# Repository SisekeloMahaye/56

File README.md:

# Group 57 Miro Mouse Project

## Overview
This repository contains the documentation for Group 57's Miro Mouse project. The Miro Mouse is a small robotic platform designed for navigating mazes autonomously.

## Team Members
- MHYSIS001: Responsible for the power subsystem.
- ZKHMUS002: Responsible for the sensing subsystem.

## Subsystems
### Power Subsystem (MHYSIS001)
The power subsystem manages the energy requirements of the Miro Mouse. It includes components such as batteries.

### Sensing Subsystem (ZKHMUS002)
The sensing subsystem is responsible for gathering information about the environment. It includes sensors such as infrared sensors, and any other sensors needed for maze navigation.

## Repository Structure
- `power_subsystem/`: Contains documentation related to the power subsystem.
- `sensing_subsystem/`: Contains documentation related to the sensing subsystem.
- `shared/`: Contains documentation shared between the subsystems.

## Installation
1. Clone this repository to your local machine.
2. Navigate to the relevant subsystem directory (`power_subsystem/` or `sensing_subsystem/`).
3. Follow the instructions in the README file located in each subsystem directory to set up and run the code.

## Contribution Guidelines
If you would like to contribute to this project, please follow these guidelines:
- Fork the repository.
- Create a new branch for your feature or bug fix.
- Make your changes.
- Test your changes thoroughly.
- Create a pull request detailing your changes.

## License
[Creative Commons Attribution 4.0 International license](https://choosealicense.com/licenses/cc-by-4.0/)

## Acknowledgements
- This project is developed as part of [Course EEE3088F] at [University of Cape Town].

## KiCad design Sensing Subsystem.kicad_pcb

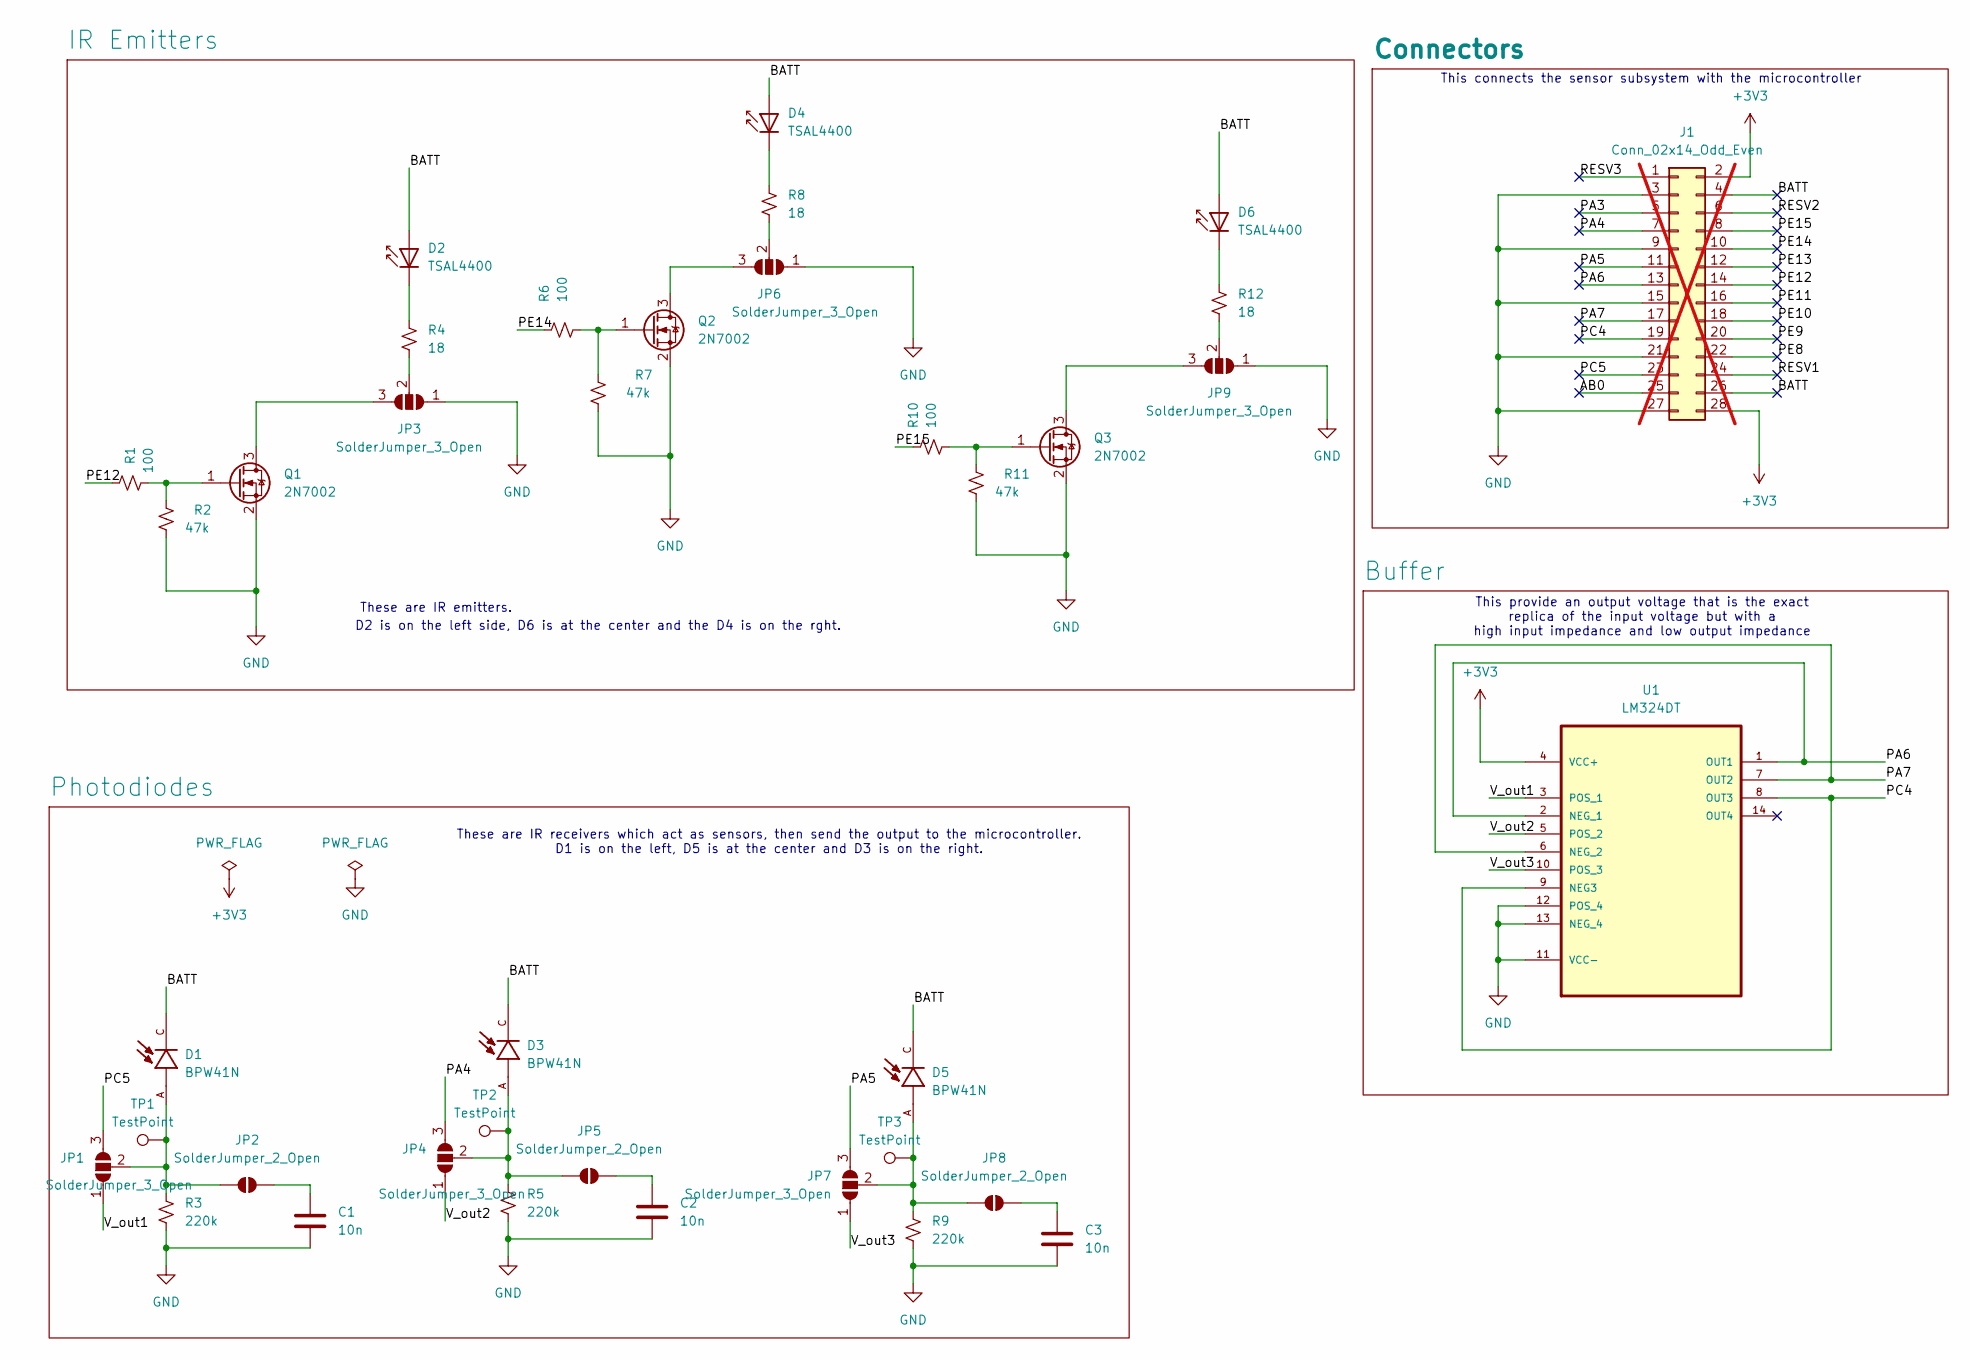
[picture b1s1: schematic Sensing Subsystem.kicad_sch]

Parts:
C1, C2, C3: 10n; C_0402_1005Metric
D1, D3, D5: BPW41N; DIO_BPW41N; PARTREV 1.6
D2, D4, D6: TSAL4400; LED_D1.8mm_W1.8mm_H2.4mm_Horizontal_O3.81mm_Z4.9mm
J1: Conn_02x14_Odd_Even; PinHeader_2x14_P1.00mm_Vertical; not fitted
JP1, JP3, JP4, JP6, JP7, JP9: SolderJumper_3_Open; SolderJumper-3_P1.3mm_Open_RoundedPad1.0x1.5mm_NumberLabels
JP2, JP5, JP8: SolderJumper_2_Open; SolderJumper-2_P1.3mm_Open_RoundedPad1.0x1.5mm
Q1, Q2, Q3: 2N7002; SOT-23
R1, R6, R10: 100; R_0402_1005Metric
R2, R7, R11: 47k; R_0402_1005Metric
R3, R5: 220k; R_0603_1608Metric
R4, R8, R12: 18; R_0402_1005Metric
R9: 220k; R_0402_1005Metric
TP1, TP2, TP3: TestPoint; TestPoint_Pad_D1.5mm
U1: LM324DT; SOIC127P600X175-14N; MPN LM324DT

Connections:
+3V3: J1.2, J1.28, U1.4 (VCC+)
/AB0: J1.25
/BATT: D1.C, D2.2 (A), D3.C, D4.2 (A), D5.C, D6.2 (A), J1.4, J1.26
/PA3: J1.5
/PA4: J1.7, JP4.3 (B)
/PA5: J1.11, JP7.3 (B)
/PA6: J1.13, U1.1 (OUT1), U1.2 (NEG_1)
/PA7: J1.17, U1.6 (NEG_2), U1.7 (OUT2)
/PC4: J1.19, U1.8 (OUT3), U1.9 (NEG3)
/PC5: J1.23, JP1.3 (B)
/PE8: J1.22
/PE9: J1.20
/PE10: J1.18
/PE11: J1.16
/PE12: J1.14, R1.1
/PE13: J1.12
/PE14: J1.10, R6.1
/PE15: J1.8, R10.1
/RESV1: J1.24
/RESV2: J1.6
/RESV3: J1.1
/V_out1: JP1.1 (A), U1.3 (POS_1)
/V_out2: JP4.1 (A), U1.5 (POS_2)
/V_out3: JP7.1 (A), U1.10 (POS_3)
GND: C1.2, C2.2, C3.2, J1.3, J1.9, J1.15, J1.21, J1.27, JP3.1 (A), JP6.1 (A), JP9.1 (A), Q1.2 (S), Q2.2 (S), Q3.2 (S), R2.2, R3.2, R5.2, R7.2, R9.2, R11.2, U1.11 (VCC-), U1.12 (POS_4), U1.13 (NEG_4)
unnamed: D2.1 (K), R4.1
unnamed: D4.1 (K), R8.1
unnamed: D6.1 (K), R12.1
unnamed: D1.A, JP1.2 (C), JP2.1 (A), R3.1, TP1.1
unnamed: C1.1, JP2.2 (B)
unnamed: JP3.3 (B), Q1.3 (D)
unnamed: JP3.2 (C), R4.2
unnamed: D3.A, JP4.2 (C), JP5.1 (A), R5.1, TP2.1
unnamed: C2.1, JP5.2 (B)
unnamed: JP6.3 (B), Q2.3 (D)
unnamed: JP6.2 (C), R8.2
unnamed: D5.A, JP7.2 (C), JP8.1 (A), R9.1, TP3.1
unnamed: C3.1, JP8.2 (B)
unnamed: JP9.3 (B), Q3.3 (D)
unnamed: JP9.2 (C), R12.2
unnamed: Q1.1 (G), R1.2, R2.1
unnamed: Q2.1 (G), R6.2, R7.1
unnamed: Q3.1 (G), R10.2, R11.1

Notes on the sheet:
This connects the sensor subsystem with the microcontroller
D2 is on the left side, D6 is at the center and the D4 is on the rght.
This provide an output voltage that is the exact replica of the input voltage but with a high input impedance and low output impedance
These are IR emitters.
These are IR receivers which act as sensors, then send the output to the microcontroller. D1 is on the left, D5 is at the center and D3 is on the right.

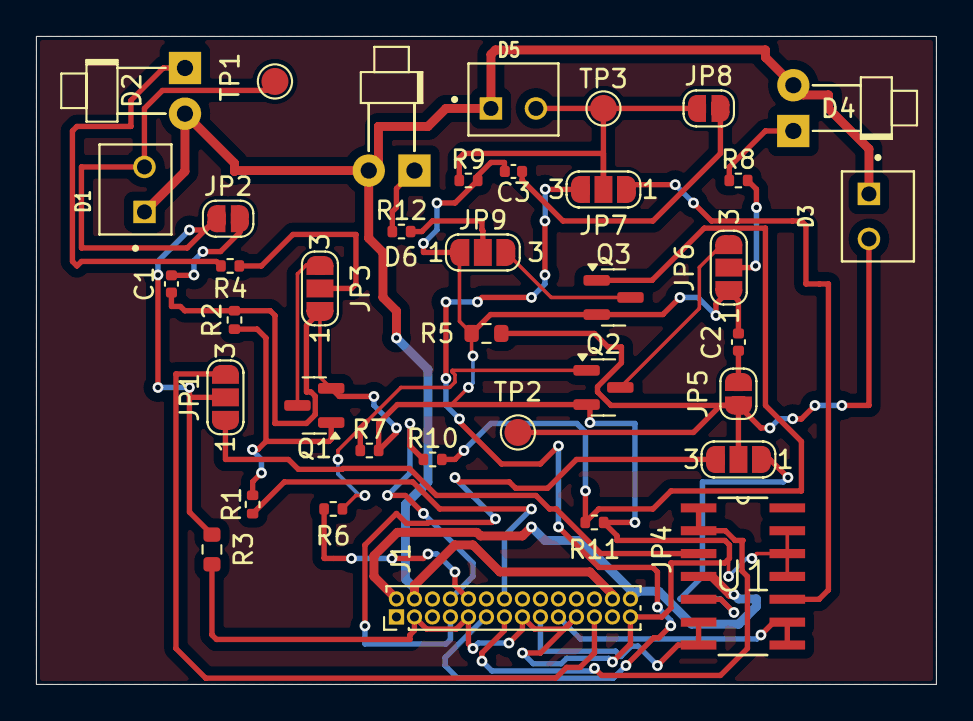
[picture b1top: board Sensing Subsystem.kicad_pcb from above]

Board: 2 copper layers, 50.0 x 36.0 mm, 38 parts (0 on the bottom side), 33 nets.

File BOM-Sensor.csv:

Comment,Designator,Footprint,LCSC
BPW41N,"D1,D3,D5",DIO_BPW41N,C142586
10n,"C1,C2,C3",C_0402_1005Metric,C15195
220k,"R3,R5,R9",R_0603_1608Metric,C22939
15,"R12,R4,R8",R_0402_1005Metric,C25756
47k,"R11,R2,R7",R_0402_1005Metric,C25792
100,"R1,R10,R6",R_0402_1005Metric,C4109
LM324DT,U1,SOIC127P600X175-14N,C71035
2N7002,"Q1,Q2,Q3",SOT-23,C8545
TSAL4400,"D2,D4,D6",LED_D1.8mm_W1.8mm_H2.4mm_Horizontal_O3.81mm_Z4.9mm,C94135

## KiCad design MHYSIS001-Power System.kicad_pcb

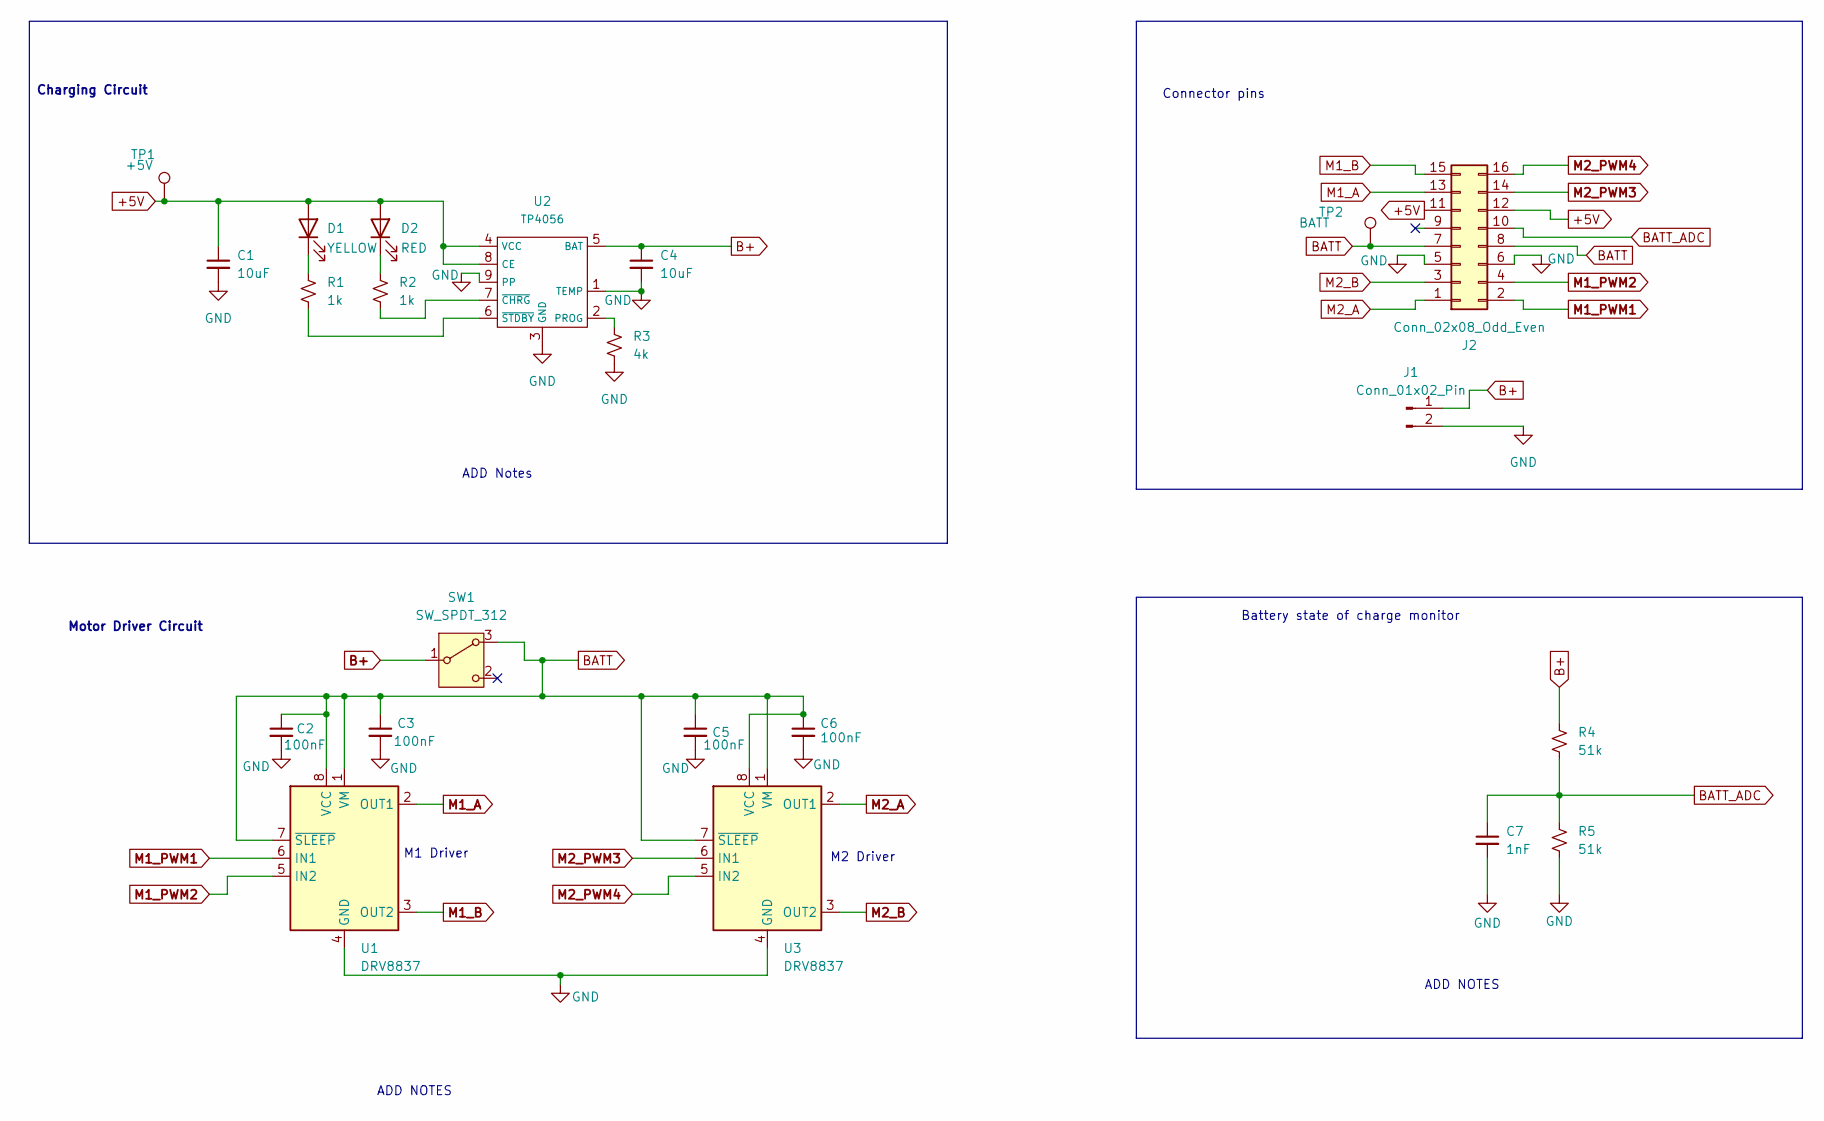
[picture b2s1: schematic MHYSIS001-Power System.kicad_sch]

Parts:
C1, C4: 10uF; C_0603_1608Metric
C2, C3, C5, C6: 100nF; C_0603_1608Metric
C7: 1nF; C_0603_1608Metric
D1: YELLOW; LED_0603_1608Metric
D2: RED; LED_0603_1608Metric
J1: Conn_01x02_Pin; JST_PH_B2B-PH-K_1x02_P2.00mm_Vertical
J2: Conn_02x08_Odd_Even; PinHeader_2x08_P2.54mm_Vertical
R1, R2: 1k; R_0603_1608Metric
R3: 4k; R_0603_1608Metric
R4, R5: 51k; R_0603_1608Metric
SW1: SW_SPDT_312; mySwitch
TP1: +5V; TestPoint_Pad_D1.0mm
TP2: BATT; TestPoint_Pad_D1.0mm
U1, U3: DRV8837; WSON-8-1EP_2x2mm_P0.5mm_EP0.9x1.6mm
U2: TP4056; SOIC-8-1EP_3.9x4.9mm_P1.27mm_EP2.29x3mm

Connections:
+5V: C1.1, D1.2 (A), D2.2 (A), J2.11, J2.12, TP1.1, U2.4 (VCC), U2.8 (CE)
B+: C4.1, J1.1, R4.1, SW1.1 (B), U2.5 (BAT)
BATT: C2.1, C3.1, C5.1, C6.1, J2.7, J2.8, SW1.3 (A), TP2.1, U1.1 (VM), U1.7 (~SLEEP), U1.8 (VCC), U3.1 (VM), U3.7 (~SLEEP), U3.8 (VCC)
BATT_ADC: C7.1, J2.10, R4.2, R5.1
GND: C1.2, C2.2, C3.2, C4.2, C5.2, C6.2, C7.2, J1.2, J2.5, J2.6, R3.2, R5.2, U1.4 (GND), U1.9 (GND), U2.1 (TEMP), U2.3 (GND), U2.9 (PP), U3.4 (GND), U3.9 (GND)
M1_A: J2.13, U1.2 (OUT1)
M1_B: J2.15, U1.3 (OUT2)
M1_PWM1: J2.2, U1.6 (IN1)
M1_PWM2: J2.4, U1.5 (IN2)
M2_A: J2.1, U3.2 (OUT1)
M2_B: J2.3, U3.3 (OUT2)
M2_PWM3: J2.14, U3.6 (IN1)
M2_PWM4: J2.16, U3.5 (IN2)
unnamed: D1.1 (K), R1.1
unnamed: D2.1 (K), R2.1
unnamed: R3.1, U2.2 (PROG)
unnamed: R2.2, U2.7 (~CHRG)
unnamed: R1.2, U2.6 (~STDBY)

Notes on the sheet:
M2 Driver
M1 Driver
ADD NOTES
Charging Circuit
ADD Notes
Motor Driver Circuit
Battery state of charge monitor
Connector pins

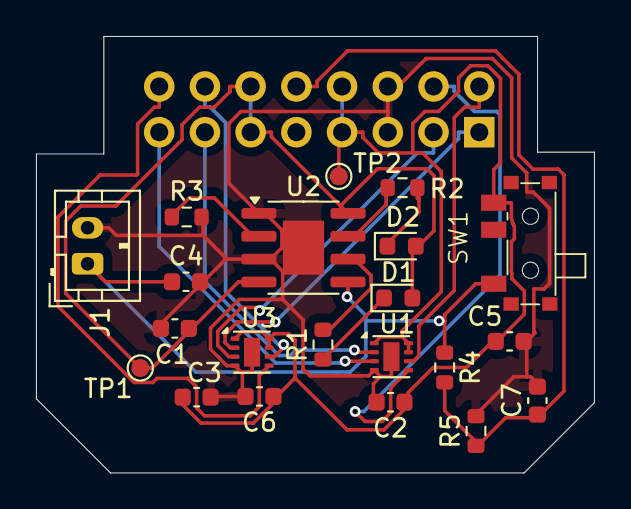
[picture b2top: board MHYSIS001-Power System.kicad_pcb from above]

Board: 2 copper layers, 31.0 x 24.2 mm, 22 parts (1 on the bottom side), 18 nets.

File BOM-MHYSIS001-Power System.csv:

Comment,Designator,Footprint,LCSC
100nF,"C2,C3,C5,C6",C_0603_1608Metric,C14663
1nF,C7,C_0603_1608Metric,C1588
DRV8837,"U1,U3",WSON-8-1EP_2x2mm_P0.5mm_EP0.9x1.6mm,C191000
10uF,"C1,C4",C_0603_1608Metric,C19702
1k,"R1,R2",R_0603_1608Metric,C21190
RED,D2,LED_0603_1608Metric,C2286
YELLOW,D1,LED_0603_1608Metric,C2296
4k,R3,R_0603_1608Metric,C22978
51k,"R4,R5",R_0603_1608Metric,C23196
SW_SPDT_312,SW1,mySwitch,C2890358
TP4056,U2,SOIC-8-1EP_3.9x4.9mm_P1.27mm_EP2.29x3mm,C725790

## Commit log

2024-04-21 Add files via upload
    Added Gerber files
2024-04-21 Add files via upload
    Added CPL files
2024-04-21 Add files via upload
    Added BOM file
2024-04-21 Add files via upload
    Added schematic
2024-04-21 Add files via upload
    Added PCB file
